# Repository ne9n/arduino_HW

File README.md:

Ki cad files

Arduino anao based timer for control line and gyto.  Uses myu 50 20 based board

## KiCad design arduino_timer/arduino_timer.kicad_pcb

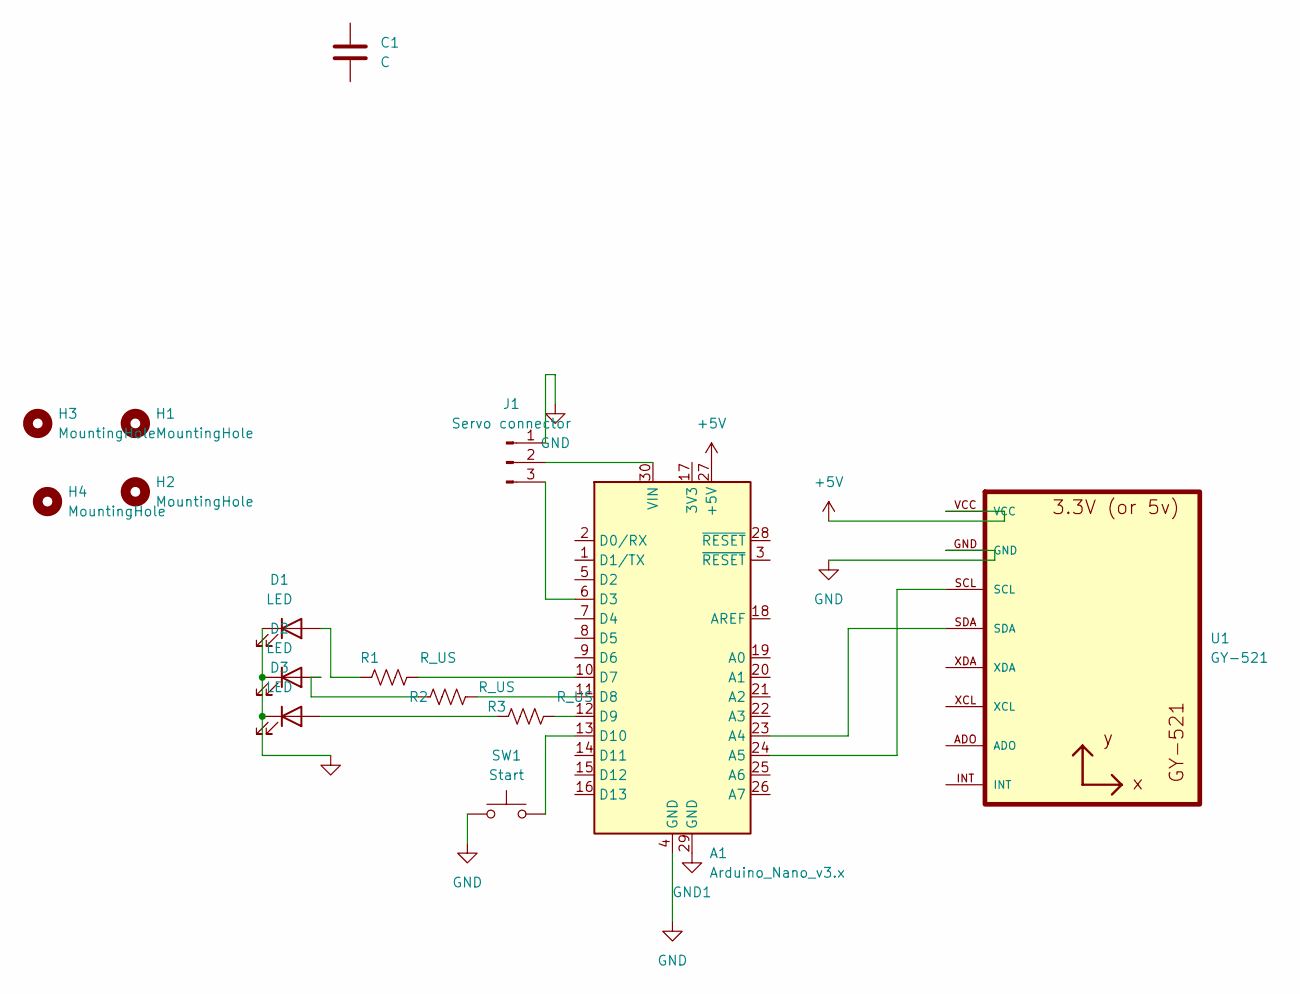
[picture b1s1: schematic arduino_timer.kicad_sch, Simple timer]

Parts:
A1: Arduino_Nano_v3.x; Arduino_Nano
C1: C
D1, D2, D3: LED; LED_D3.0mm
H1, H2, H3, H4: MountingHole; MountingHole_2.2mm_M2
J1: Servo connector; PinHeader_1x03_P2.54mm_Vertical
R1, R2, R3: R_US; R_Axial_DIN0207_L6.3mm_D2.5mm_P2.54mm_Vertical
SW1: Start; SW_PUSH_6mm_H8.5mm
U1: GY-521

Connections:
+5V: A1.27 (+5V), U1.VCC
GND: A1.4 (GND), D1.1 (K), D2.1 (K), D3.1 (K), J1.1, SW1.1, U1.GND
GND1: A1.29 (GND)
unnamed: A1.23 (A4), U1.SDA
unnamed: A1.24 (A5), U1.SCL
unnamed: A1.6 (D3), J1.3
unnamed: A1.10 (D7), R1.2
unnamed: A1.11 (D8), R2.2
unnamed: A1.12 (D9), R3.2
unnamed: A1.13 (D10), SW1.2
unnamed: A1.30 (VIN), J1.2
unnamed: D1.2 (A), R1.1
unnamed: D2.2 (A), R2.1
unnamed: D3.2 (A), R3.1

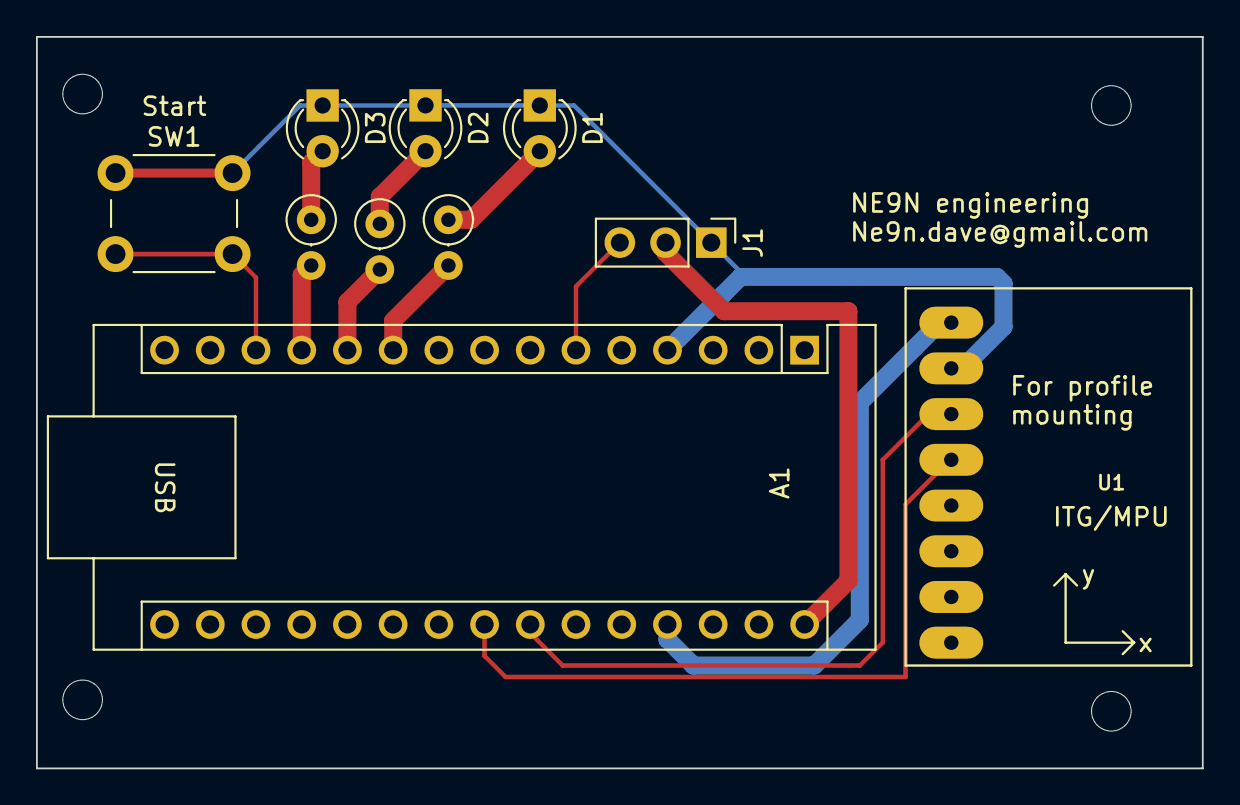
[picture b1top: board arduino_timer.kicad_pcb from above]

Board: 2 copper layers, 64.8 x 40.6 mm, 14 parts (0 on the bottom side), 13 nets.

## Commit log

2024-04-10 initial commit version 3.
2024-07-05 Add files via upload
    first release used at AirVenture 2024
